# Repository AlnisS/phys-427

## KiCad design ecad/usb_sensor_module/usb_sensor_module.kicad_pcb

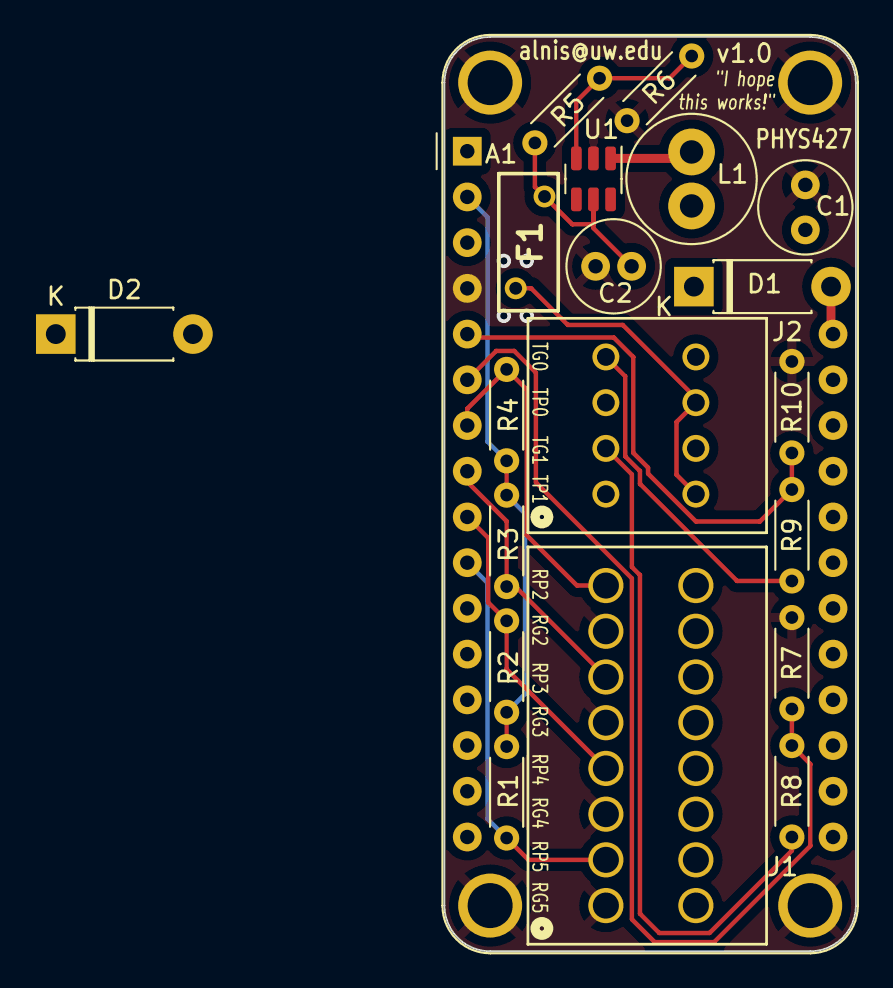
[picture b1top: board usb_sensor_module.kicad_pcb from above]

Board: 2 copper layers, 22.9 x 50.8 mm, 20 parts (0 on the bottom side), 17 nets.

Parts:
A1: Adafruit_Feather_Generic; Adafruit_Feather
C1: 4.7uF; C_Radial_D5.0mm_H11.0mm_P2.00mm
C2: 10uF; C_Radial_D5.0mm_H11.0mm_P2.00mm
D1, D2: 1N5817; D_DO-41_SOD81_P7.62mm_Horizontal
F1: 0ZRE0005FF1C
J1: 218-508; ul_218-508
J2: 218-504/000-604; ul_218-504-000-604
L1: 12uH; L_Radial_D7.0mm_P3.00mm
R1, R2, R3, R4: 10k; R_Axial_DIN0204_L3.6mm_D1.6mm_P5.08mm_Horizontal
R5: 2.0M; R_Axial_DIN0204_L3.6mm_D1.6mm_P5.08mm_Horizontal
R6: 68k; R_Axial_DIN0204_L3.6mm_D1.6mm_P5.08mm_Horizontal
R7, R10: 49.9; R_Axial_DIN0204_L3.6mm_D1.6mm_P5.08mm_Horizontal
R8, R9: 348; R_Axial_DIN0204_L3.6mm_D1.6mm_P5.08mm_Horizontal
U1: TLV61046ADB; SOT-23-6

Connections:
3V3: A1.2 (3V3), R1.1, R2.1, R3.1, R4.1
24V: F1.2, J2.2, J2.6
A0: A1.5 (A0), R9.2, R10.1
A1: A1.6 (A1), R7.1, R8.2
A2: A1.7 (A2), J1.15, R4.2
A3: A1.8 (A3), J1.11, R3.2
A4: A1.9 (A4), J1.7, R2.2
A5: A1.10 (A5), J1.3, R1.2
FB: R5.2, R6.1, U1.3 (FB)
GND: A1.4 (GND), C1.2, C2.2, J1.1, J1.5, J1.9, J1.13, R6.2, R7.2, R10.2, U1.2 (GND)
unnamed: C1.1, D1.1 (K), D2.1 (K), L1.1, U1.4 (EN), U1.6 (VI)
unnamed: J2.3, R8.1
unnamed: J2.7, R9.1
unnamed: C2.1, F1.1, R5.1, U1.5 (VOUT)
SW: L1.2, U1.1 (SW)
USB: A1.26 (USB), D2.2 (A)
VBAT: A1.28 (VBAT), D1.2 (A)

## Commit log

2024-01-17 Empty rocket controls project
2024-02-27 v1.0 of schematic + PCB
2024-02-27 Plot for JLCPCB
2024-04-26 USB sensor module schematic & pcb update WIP
2024-04-26 Initial Godot project for GoPIP
2024-04-26 Minimal proof of concept reading WebSerial in Godot
2024-04-26 Some basic graphing code for GoPIP
2024-04-26 Fancier graphing
2024-04-26 More GoPIP UI work
